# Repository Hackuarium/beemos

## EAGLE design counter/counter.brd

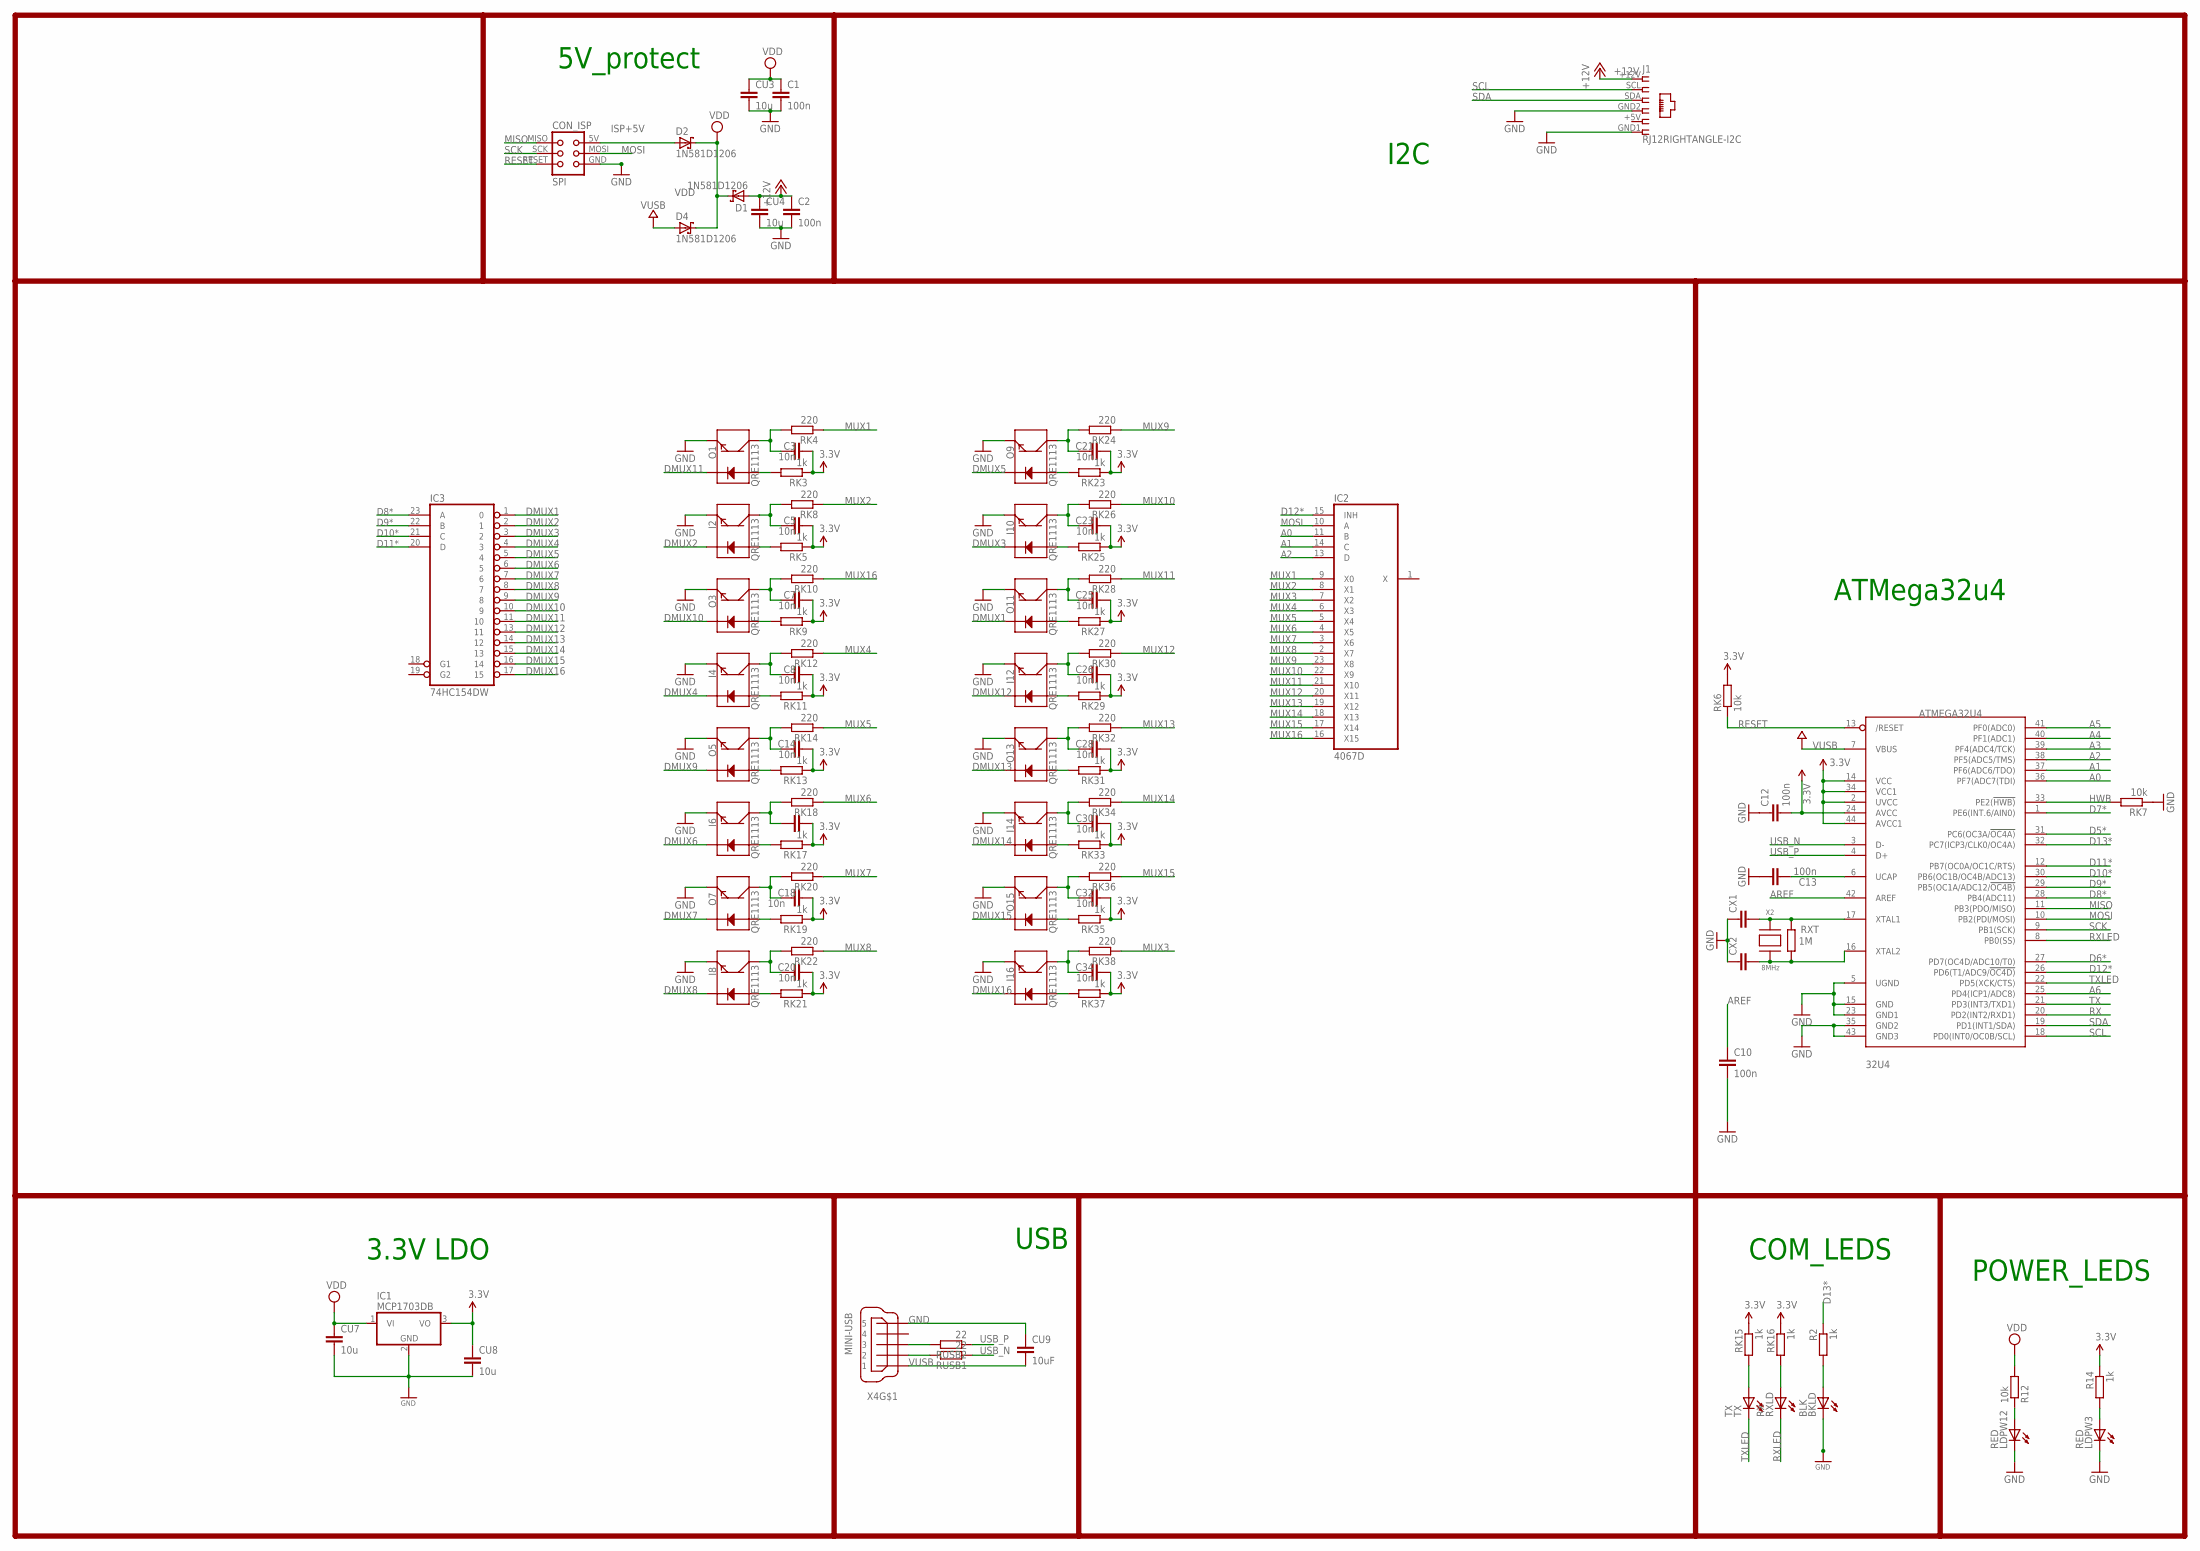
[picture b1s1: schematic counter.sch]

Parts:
32U4: ATMEGA32U4; TQFP44
BKLD: BLK; CHIP-LED0805
C1, C2, C10, C12, C13: 100n; C0805
C3, C5, C7, C8, C14, C15, C18, C20, C21, C23, C25, C26, C28, C30, C32, C34: 10n; C0805
CON_ISP: SPI; TC2030-MCP-NL
CU3, CU4, CU7, CU8: 10u; C0805
CU9: 10uF; C0805
CX1, CX2: 22pF; C0805
D1, D2, D4: 1N581D1206; LED-1206
I2, I4, I6, I8, I10, I12, I14, I16: QRE1113
IC1: MCP1703DB; SOT223
IC2: 4067D; SO24W
IC3: 74HC154DW; SO24W
J1: RJ12RIGHTANGLE-I2C; RJ12-RIGHTANGLE-I2C
LDPW3, LDPW12: RED; CHIP-LED0805
O1, O3, O5, O7, O9, O11, O13, O15: QRE1113
R2, R14: 1k; R0805
R12: 10k; R0805
RK3, RK5, RK9, RK11, RK13, RK17, RK19, RK21, RK23, RK25, RK27, RK29, RK31, RK33, RK35, RK37: 1k; M0805
RK4, RK8, RK10, RK12, RK14, RK18, RK20, RK22, RK24, RK26, RK28, RK30, RK32, RK34, RK36, RK38: 220; M0805
RK6, RK7: 10k; M0805
RK15, RK16: 1k; R0805
RUSB1, RUSB2: 22; M0805
RXLD: RX; CHIP-LED0805
RXT: 1M; R0805
TX: TX; CHIP-LED0805
X2: 8MHz; NX6035
X4: MINI-USB; 32005-201

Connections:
3.3V: 32U4.2 (UVCC), 32U4.14 (VCC), 32U4.24 (AVCC), 32U4.34 (VCC1), 32U4.44 (AVCC1), C3.2, C5.2, C7.2, C8.2, C12.2, C14.2, C15.2, C18.2, C20.2, C21.2, C23.2, C25.2, C26.2, C28.2, C30.2, C32.2, C34.2, CU8.1, IC1.3 (VO), R14.1, RK3.1, RK5.1, RK6.2, RK9.1, RK11.1, RK13.1, RK15.1, RK16.1, RK17.1, RK19.1, RK21.1, RK23.1, RK25.1, RK27.1, RK29.1, RK31.1, RK33.1, RK35.1, RK37.1
5: J1.+5V (5)
+12V: C2.1, CU4.1, D1.A, J1.+12V (1)
A0: 32U4.36 (PF7(ADC7(TDI)), IC2.11 (B)
A1: 32U4.37 (PF6(ADC6/TDO)), IC2.14 (C)
A2: 32U4.38 (PF5(ADC5/TMS)), IC2.13 (D)
A3: 32U4.39 (PF4(ADC4/TCK))
A4: 32U4.40 (PF1(ADC1))
A5: 32U4.41 (PF0(ADC0))
A6: 32U4.25 (PD4(ICP1/ADC8))
AREF: 32U4.42 (AREF), C10.1
D5*: 32U4.31 (PC6(OC3A/!OC4A))
D6*: 32U4.27 (PD7(OC4D/ADC10/T0))
D7*: 32U4.1 (PE6(INT.6/AIN0))
D8*: 32U4.28 (PB4(ADC11)), IC3.23 (A)
D9*: 32U4.29 (PB5(OC1A/ADC12/!OC4B)), IC3.22 (B)
D10*: 32U4.30 (PB6(OC1B/OC4B/ADC13)), IC3.21 (C)
D11*: 32U4.12 (PB7(OC0A/OC1C/RTS)), IC3.20 (D)
D12*: 32U4.26 (PD6(T1/ADC9/!OC4D)), IC2.15 (INH)
D13*: 32U4.32 (PC7(ICP3/CLK0/OC4A)), R2.1
DMUX1: IC3.1 (0), O11.2 (K)
DMUX2: I2.2 (K), IC3.2 (1)
DMUX3: I10.2 (K), IC3.3 (2)
DMUX4: I4.2 (K), IC3.4 (3)
DMUX5: IC3.5 (4), O9.2 (K)
DMUX6: I6.2 (K), IC3.6 (5)
DMUX7: IC3.7 (6), O7.2 (K)
DMUX8: I8.2 (K), IC3.8 (7)
DMUX9: IC3.9 (8), O5.2 (K)
DMUX10: IC3.10 (9), O3.2 (K)
DMUX11: IC3.11 (10), O1.2 (K)
DMUX12: I12.2 (K), IC3.13 (11)
DMUX13: IC3.14 (12), O13.2 (K)
DMUX14: I14.2 (K), IC3.15 (13)
DMUX15: IC3.16 (14), O15.2 (K)
DMUX16: I16.2 (K), IC3.17 (15)
GND: 32U4.5 (UGND), 32U4.15 (GND), 32U4.23 (GND1), 32U4.35 (GND2), 32U4.43 (GND3), BKLD.C, C1.2, C2.2, C10.2, C12.1, C13.1, CON_ISP.GND, CU3.2, CU4.2, CU7.2, CU8.2, CU9.1, CX1.1, CX2.1, I2.4 (E), I4.4 (E), I6.4 (E), I8.4 (E), I10.4 (E), I12.4 (E), I14.4 (E), I16.4 (E), IC1.2 (GND), IC3.12 (GND), J1.GND1 (6), J1.GND2 (4), LDPW3.C, LDPW12.C, O1.4 (E), O3.4 (E), O5.4 (E), O7.4 (E), O9.4 (E), O11.4 (E), O13.4 (E), O15.4 (E), RK7.1, X4.5
HWB: 32U4.33 (PE2(!HWB)), RK7.2
ISP+5V: CON_ISP.5V (VCC), D2.A
MISO: 32U4.11 (PB3(PDO/MISO)), CON_ISP.MISO
MOSI: 32U4.10 (PB2(PDI/MOSI)), CON_ISP.MOSI, IC2.10 (A)
MUX1: IC2.9 (X0), RK4.1
MUX2: IC2.8 (X1), RK8.1
MUX3: IC2.7 (X2), RK38.1
MUX4: IC2.6 (X3), RK12.1
MUX5: IC2.5 (X4), RK14.1
MUX6: IC2.4 (X5), RK18.1
MUX7: IC2.3 (X6), RK20.1
MUX8: IC2.2 (X7), RK22.1
MUX9: IC2.23 (X8), RK24.1
MUX10: IC2.22 (X9), RK26.1
MUX11: IC2.21 (X10), RK28.1
MUX12: IC2.20 (X11), RK30.1
MUX13: IC2.19 (X12), RK32.1
MUX14: IC2.18 (X13), RK34.1
MUX15: IC2.17 (X14), RK36.1
MUX16: IC2.16 (X15), RK10.1
unnamed: 32U4.6 (UCAP), C13.2
unnamed: O3.1 (A), RK9.2
unnamed: BKLD.A, R2.2
unnamed: O1.1 (A), RK3.2
unnamed: C3.1, O1.3 (C), RK4.2
unnamed: LDPW12.A, R12.1
unnamed: I2.1 (A), RK5.2
unnamed: C5.1, I2.3 (C), RK8.2
unnamed: C7.1, O3.3 (C), RK10.2
unnamed: I4.1 (A), RK11.2
unnamed: RK15.2, TX.A
unnamed: C8.1, I4.3 (C), RK12.2
unnamed: O9.1 (A), RK23.2
unnamed: O5.1 (A), RK13.2
unnamed: C14.1, O5.3 (C), RK14.2
unnamed: RK16.2, RXLD.A
unnamed: I6.1 (A), RK17.2
unnamed: C15.1, I6.3 (C), RK18.2
unnamed: C21.1, O9.3 (C), RK24.2
unnamed: O7.1 (A), RK19.2
unnamed: C18.1, O7.3 (C), RK20.2
unnamed: LDPW3.A, R14.2
unnamed: I10.1 (A), RK25.2
unnamed: C23.1, I10.3 (C), RK26.2
unnamed: I8.1 (A), RK21.2
unnamed: C20.1, I8.3 (C), RK22.2
unnamed: O11.1 (A), RK27.2
unnamed: C25.1, O11.3 (C), RK28.2
unnamed: 32U4.17 (XTAL1), CX1.2, RXT.2, X2.P$2
unnamed: I12.1 (A), RK29.2
unnamed: C26.1, I12.3 (C), RK30.2
unnamed: O13.1 (A), RK31.2
unnamed: C28.1, O13.3 (C), RK32.2
unnamed: I14.1 (A), RK33.2
unnamed: C30.1, I14.3 (C), RK34.2
unnamed: O15.1 (A), RK35.2
unnamed: C32.1, O15.3 (C), RK36.2
unnamed: I16.1 (A), RK37.2
unnamed: C34.1, I16.3 (C), RK38.2
RESET: 32U4.13 (/RESET), CON_ISP.RESET, RK6.1
RX: 32U4.20 (PD2(INT2/RXD1))
RXLED: 32U4.8 (PB0(SS)), RXLD.C
SCK: 32U4.9 (PB1(SCK)), CON_ISP.SCK
SCL: 32U4.18 (PD0(INT0/OC0B/SCL)), J1.SCL (2)
SDA: 32U4.19 (PD1(INT1/SDA)), J1.SDA (3)
TX: 32U4.21 (PD3(INT3/TXD1))
TXLED: 32U4.22 (PD5(XCK/CTS)), TX.C
USBC_N: RUSB1.2, X4.2
USBC_P: RUSB2.2, X4.3
USB_N: 32U4.3 (D-), RUSB1.1
USB_P: 32U4.4 (D+), RUSB2.1
VCC: IC3.24 (VCC)
VDD: C1.1, CU3.1, CU7.1, D1.C, D2.C, D4.C, IC1.1 (VI), IC2.24 (VDD), R12.2
VSS: IC2.12 (VSS)
VUSB: 32U4.7 (VBUS), CU9.2, D4.A, X4.1
XTAL1: 32U4.16 (XTAL2), CX2.2, RXT.1, X2.P$1

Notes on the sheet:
USB
I2C
5V_protect
POWER_LEDS
COM_LEDS
3.3V LDO
ATMega32u4

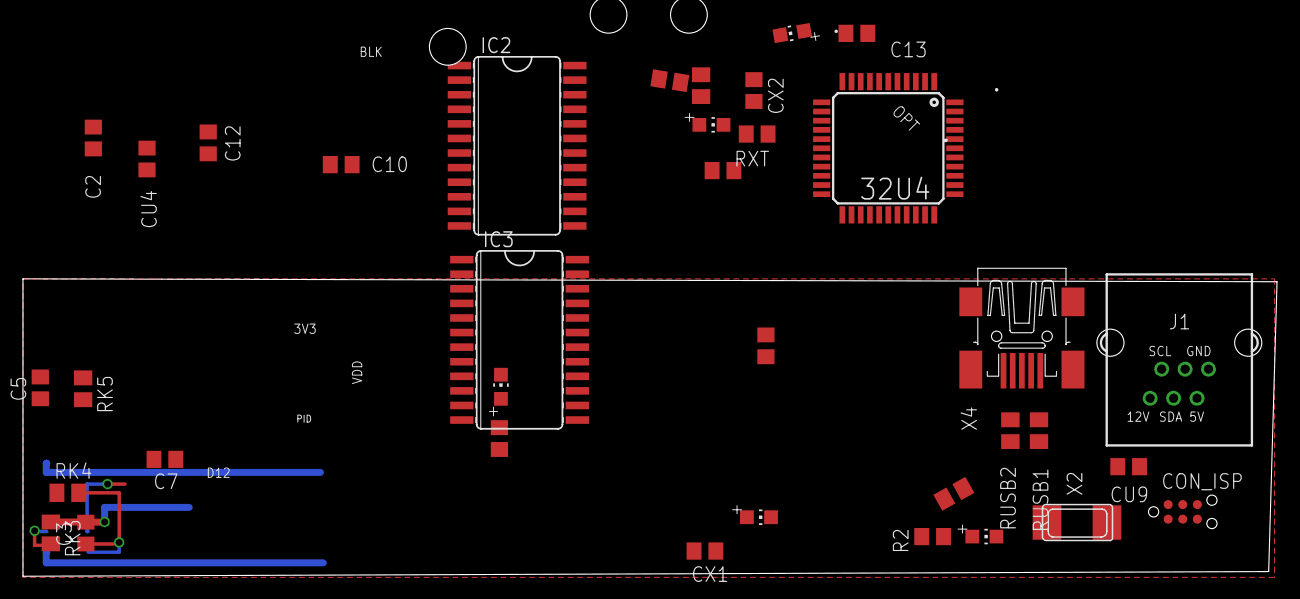
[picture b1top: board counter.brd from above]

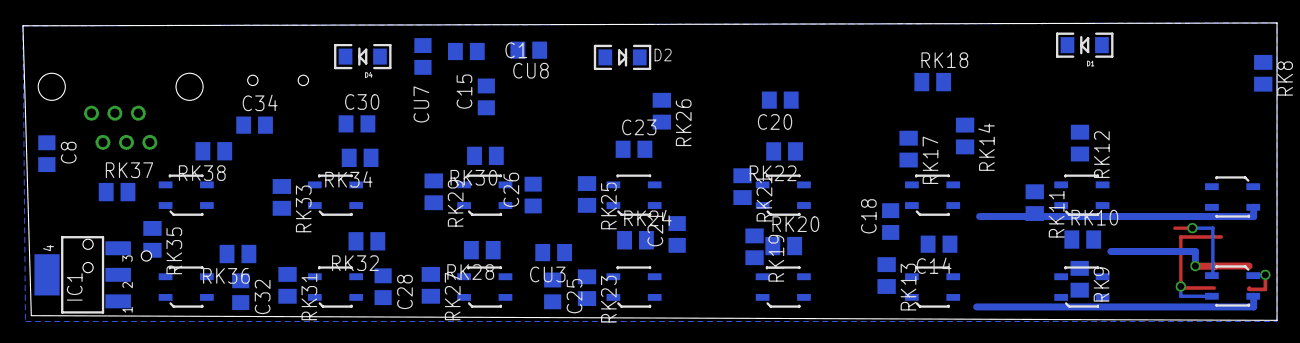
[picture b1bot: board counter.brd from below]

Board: 4 copper layers, 109.2 x 25.9 mm, 102 parts (66 on the bottom side), 101 nets.

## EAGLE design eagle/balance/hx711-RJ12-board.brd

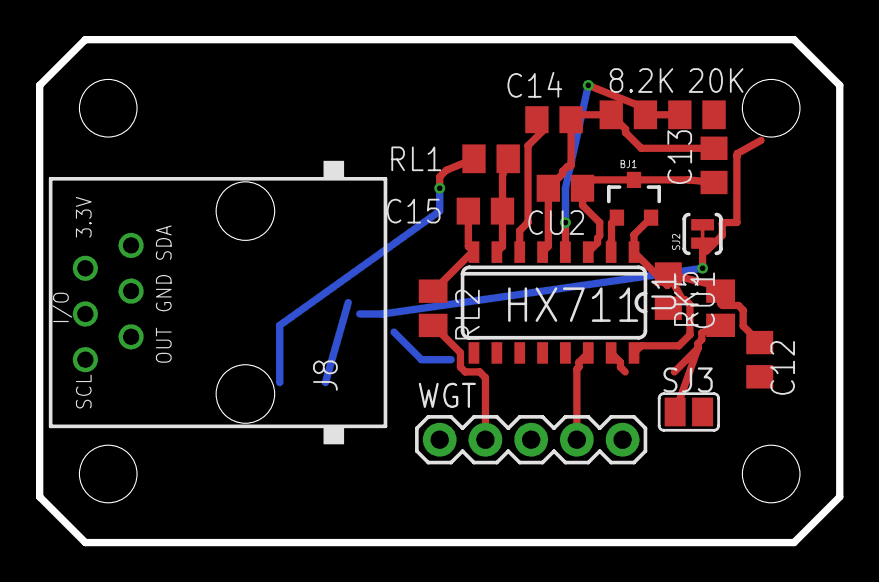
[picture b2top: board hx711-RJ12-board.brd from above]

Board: 2 copper layers, 44.5 x 27.9 mm, 17 parts (0 on the bottom side), 12 nets.

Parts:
8.2K: 8.2k; M0805
20K: 20k; M0805
BJ1: MMBT4403; SOT23-3
C12, C13, C14, C15: 100n; C0805
CU1, CU2: 10u; C0805
J8: RJ123.3; RJ12-STRAIGHT-3.3
RK5: 10k; M0805
RL1, RL2: 100; M0805
SJ2: PAD-JUMPER-2-NC_BY_TRACE_YES_SILK
SJ3: SJ
U1: HX711; SO16
WGT: 1X05

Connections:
3.3V: BJ1.2, C12.1, CU1.1, RK5.2, U1.1, U1.16
A+: RL2.2, WGT.2
A-: RL1.2, WGT.3
CN3: C14.2, U1.6
GND: C12.2, CU1.2, SJ2.1, SJ3.2, U1.14, WGT.1, WGT.4
LGND: 8.2K.1, C13.2, C14.1, CU2.2, SJ2.2, U1.5
unnamed: 20K.2, BJ1.3, C13.1, CU2.1, U1.3, WGT.5
unnamed: C15.2, RL1.1, U1.7
unnamed: BJ1.1, U1.2
unnamed: 8.2K.2, 20K.1, U1.4
unnamed: RK5.1, SJ3.1, U1.15
unnamed: C15.1, RL2.1, U1.8

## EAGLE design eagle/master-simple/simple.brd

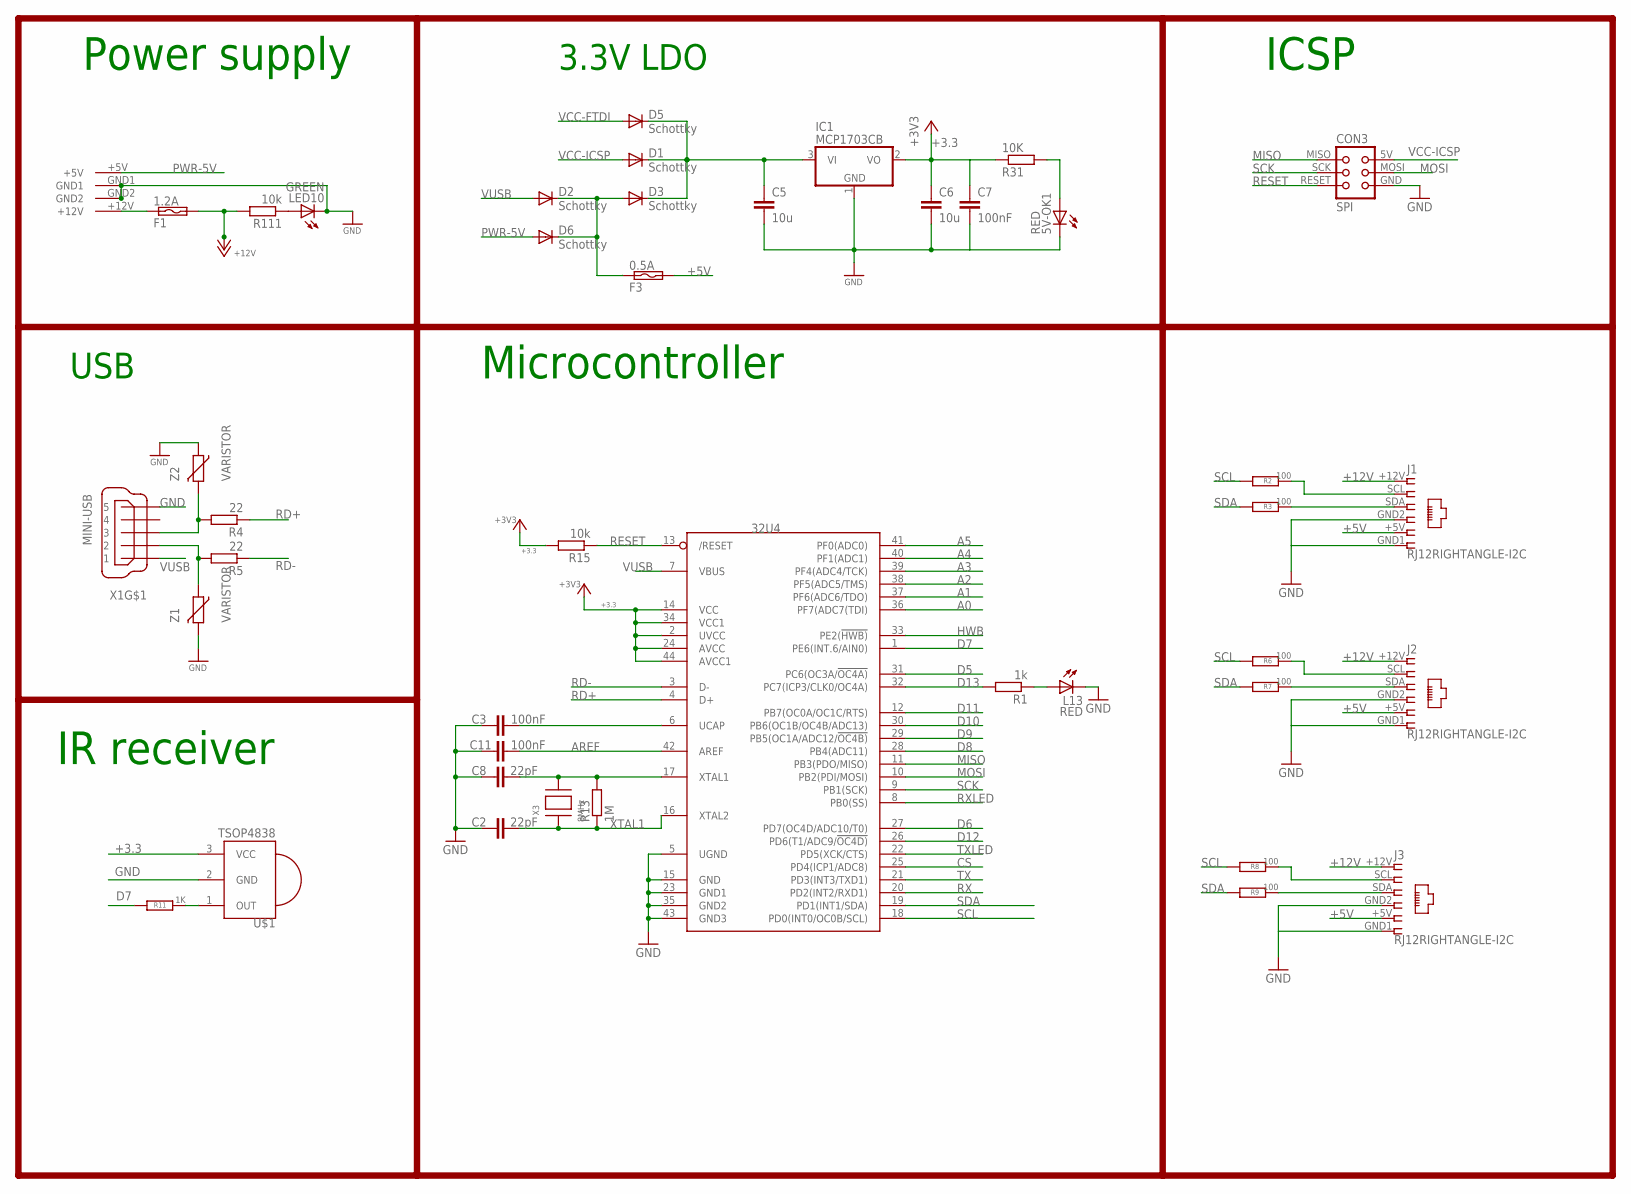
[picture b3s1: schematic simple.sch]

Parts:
5V-OK1: RED; CHIP-LED0805
C2, C8: 22pF; C0805K
C3, C11: 100nF; C0805K
C5, C6: 10u; C0805K; MPN 77-VJ1206V106ZXQTBC; LCSC C15850
C7: 100nF; C0805K; MPN 80-C1206C104K5R; LCSC C49678
CON3: SPI; TC2030-MCP-NL
D1, D2, D3, D5, D6: Schottky; SOD123; MPN 621-1N5819HW-F; LCSC C82544
F1: 1.2A; C1812
F3: 0.5A; C1812
IC1: MCP1703CB; SOT23; LCSC C53352
J1, J2, J3: RJ12RIGHTANGLE-I2C; RJ12-RIGHTANGLE-I2C
L13: RED; CHIP-LED0805
LED10: GREEN; CHIP-LED0805
R1: 1k; M0805
R2, R3, R6, R7, R8, R9: 100; R0805
R4, R5: 22; R0805; LCSC C17561
R11: 1K; R0805
R13: 1M; M0805
R15: 10k; M0805
R31: 10K; R0805
R111: 10k; R0805
U$1: TSOP4838; PNA460XM
U$4: 32U4; TQFP44
U$6: KPJX-4S-S
X1: MINI-USB; 32005-201; MPN 649-10033526-N3212LF; LCSC C46391
X3: 8MHz; NX6035
Z1, Z2: VARISTOR; CT/CN0603

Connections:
+3V3: C6.1, C7.1, IC1.2 (VO), R15.2, R31.1, U$1.3 (VCC), U$4.2 (UVCC), U$4.14 (VCC), U$4.24 (AVCC), U$4.34 (VCC1), U$4.44 (AVCC1); also elsewhere on the board
+5V: F3.2, J1.+5V (5), J2.+5V (5), J3.+5V (5); also elsewhere on the board
+12V: F1.2, J1.+12V (1), J2.+12V (1), J3.+12V (1), R111.2
+XV: C5.1, D1.C, D3.C, D5.C, IC1.3 (VI)
A0: U$4.36 (PF7(ADC7(TDI))
A1: U$4.37 (PF6(ADC6/TDO))
A2: U$4.38 (PF5(ADC5/TMS))
A3: U$4.39 (PF4(ADC4/TCK))
A4: U$4.40 (PF1(ADC1))
A5: U$4.41 (PF0(ADC0))
AREF: C11.1, U$4.42 (AREF)
CS: U$4.25 (PD4(ICP1/ADC8))
D5: U$4.31 (PC6(OC3A/!OC4A))
D6: U$4.27 (PD7(OC4D/ADC10/T0))
D7: R11.2, U$4.1 (PE6(INT.6/AIN0))
D8: U$4.28 (PB4(ADC11))
D9: U$4.29 (PB5(OC1A/ADC12/!OC4B))
D10: U$4.30 (PB6(OC1B/OC4B/ADC13))
D11: U$4.12 (PB7(OC0A/OC1C/RTS))
D12: U$4.26 (PD6(T1/ADC9/!OC4D))
D13: R1.2, U$4.32 (PC7(ICP3/CLK0/OC4A))
GND: 5V-OK1.C, C2.1, C3.1, C5.2, C6.2, C7.2, C8.1, C11.2, CON3.GND, IC1.1 (GND), J1.GND1 (6), J1.GND2 (4), J2.GND1 (6), J2.GND2 (4), J3.GND1 (6), J3.GND2 (4), L13.C, LED10.C, U$1.2 (GND), U$4.5 (UGND), U$4.15 (GND), U$4.23 (GND1), U$4.35 (GND2), U$4.43 (GND3), U$6.GND1, U$6.GND2, X1.5, Z1.2, Z2.1; also elsewhere on the board
HWB: U$4.33 (PE2(!HWB))
MISO: CON3.MISO, U$4.11 (PB3(PDO/MISO))
MOSI: CON3.MOSI, U$4.10 (PB2(PDI/MOSI))
unnamed: J2.SCL (2), R6.1
unnamed: J1.SCL (2), R2.1
unnamed: J1.SDA (3), R3.1
unnamed: L13.A, R1.1
unnamed: D2.C, D3.A, D6.C, F3.1
unnamed: J2.SDA (3), R7.1
unnamed: J3.SCL (2), R8.1
unnamed: J3.SDA (3), R9.1
unnamed: R11.1, U$1.1 (OUT)
unnamed: 5V-OK1.A, R31.2
unnamed: C3.2, U$4.6 (UCAP)
unnamed: F1.1, U$6.+12V
unnamed: C8.2, R13.2, U$4.17 (XTAL1), X3.P$2
unnamed: LED10.A, R111.1
PWR-5V: D6.A, U$6.+5V
RD+: R4.1, U$4.4 (D+)
RD-: R5.1, U$4.3 (D-)
RESET: CON3.RESET, R15.1, U$4.13 (/RESET)
RX: U$4.20 (PD2(INT2/RXD1)); also elsewhere on the board
RXLED: U$4.8 (PB0(SS))
SCK: CON3.SCK, U$4.9 (PB1(SCK))
SCL: R2.2, R6.2, R8.2, U$4.18 (PD0(INT0/OC0B/SCL))
SDA: R3.2, R7.2, R9.2, U$4.19 (PD1(INT1/SDA))
TX: U$4.21 (PD3(INT3/TXD1)); also elsewhere on the board
TXLED: U$4.22 (PD5(XCK/CTS))
USBC_N: R5.2, X1.2, Z1.1
USBC_P: R4.2, X1.3, Z2.2
VCC-ICSP: CON3.5V (VCC), D1.A
VUSB: D2.A, U$4.7 (VBUS), X1.1
XTAL1: C2.2, R13.1, U$4.16 (XTAL2), X3.P$1

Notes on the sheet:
IR receiver
ICSP
Microcontroller
USB
3.3V LDO
Power supply

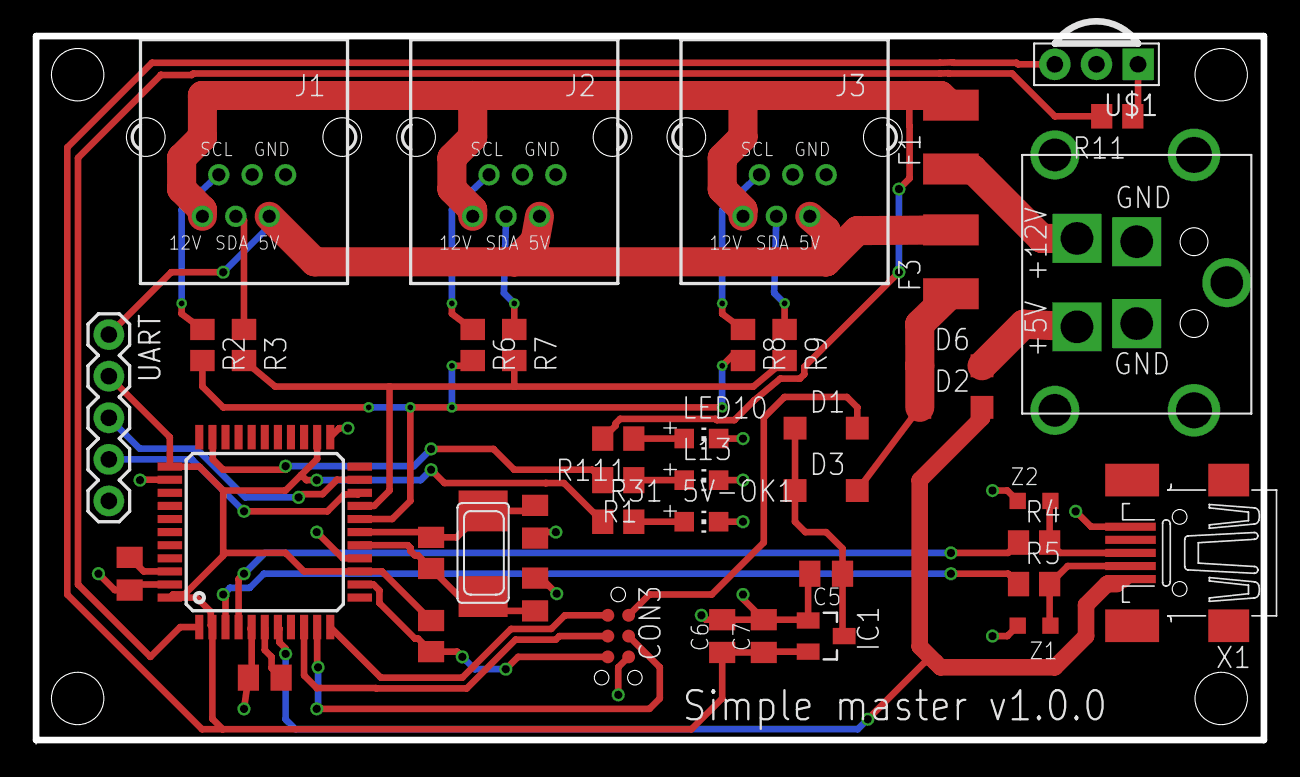
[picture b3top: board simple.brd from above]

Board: 2 copper layers, 75.0 x 43.0 mm, 43 parts (0 on the bottom side), 38 nets.

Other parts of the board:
UART: 1X05

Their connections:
+3V3: UART.2; also elsewhere on the board
+5V: UART.1; also elsewhere on the board
GND: UART.5; also elsewhere on the board
RX: UART.4; also elsewhere on the board
TX: UART.3; also elsewhere on the board

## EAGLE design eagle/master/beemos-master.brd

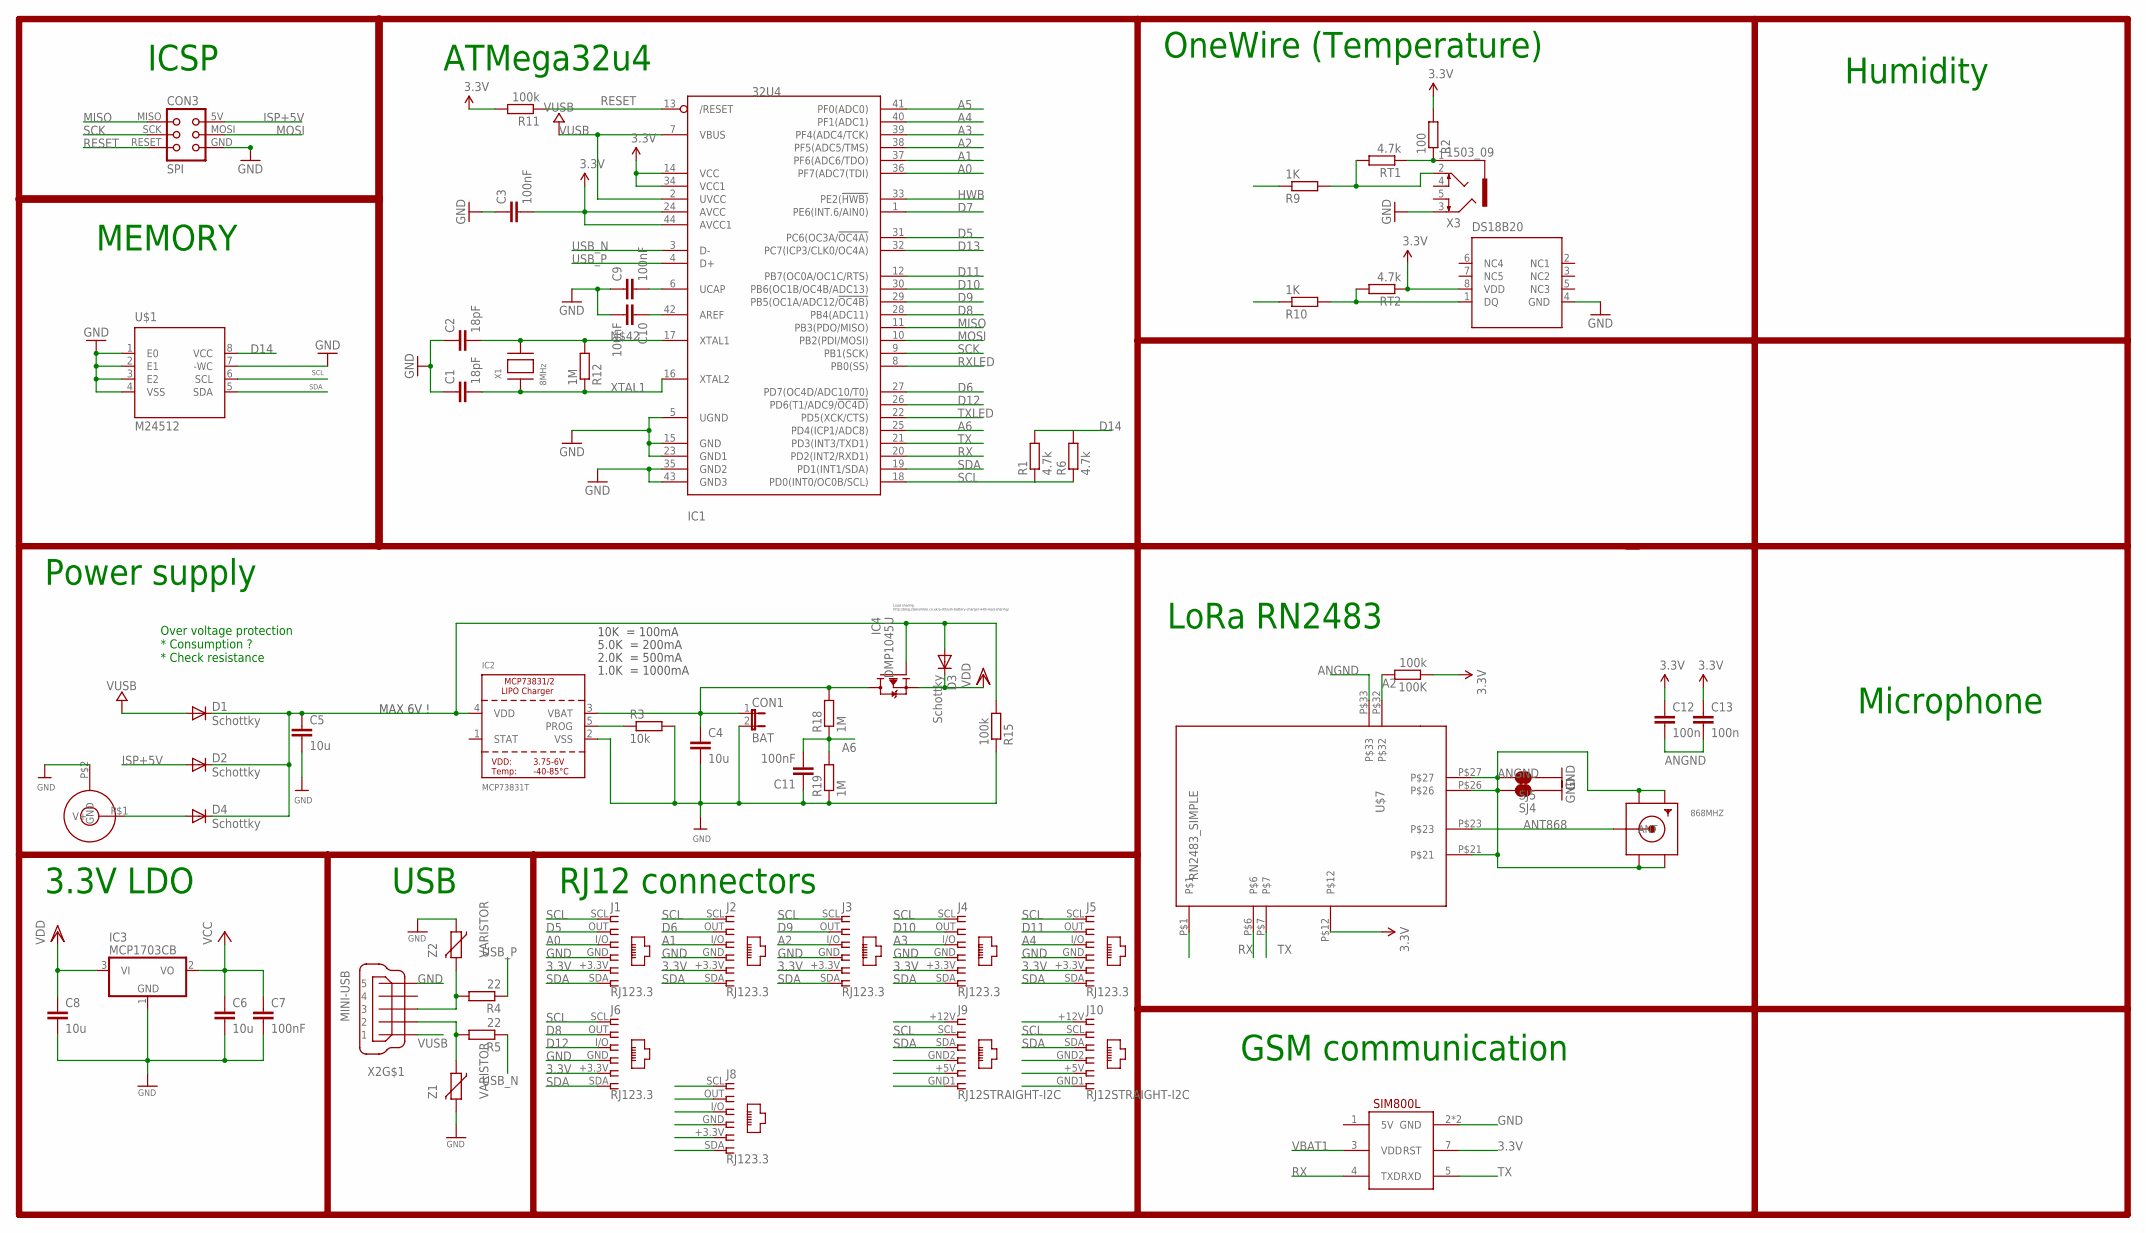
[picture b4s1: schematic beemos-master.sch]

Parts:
100K: 100k; R0805
868MHZ: SMACONNECTOR_EDGE_UFL; SMA_EDGELAUNCH_UFL
C1, C2: 18pF; C0805K; MPN 77-VJ1206A180JXXPBC; LCSC C1797
C3, C7, C9, C10, C11: 100nF; C0805K; MPN 80-C1206C104K5R; LCSC C49678
C4, C5, C6, C8: 10u; C0805K; MPN 77-VJ1206V106ZXQTBC; LCSC C15850
C12, C13: 100n; C0805
CON1: BAT; JP1
CON2: JACK_DC_BARREL; DC_BARREL
CON3: SPI; TC2030-MCP-NL
D1, D2, D3, D4: Schottky; SOD123; MPN 621-1N5819HW-F; LCSC C82544
IC1: 32U4; TQFP44; MPN 556-ATMEGA32U4RC-AU; LCSC C44854
IC2: MCP73831T; SOT23-5; MPN 579-MCP73831T-3ACIOT; LCSC C14879
IC3: MCP1703CB; SOT23; LCSC C53352
IC4: DMP1045U; SOT-23; MPN 621-DMP1045U-7; LCSC C96613
J1, J2, J3, J4, J5, J6, J8: RJ123.3; RJ12-STRAIGHT-3.3
J9, J10: RJ12STRAIGHT-I2C; RJ12-STRAIGHT-I2C
R1, R6: 4.7k; R0805
R2: 100; R0805
R3: 10k; R0805; LCSC C17414
R4, R5: 22; R0805; LCSC C17561
R9, R10: 1K; R0805
R11, R15: 100k; R0805; MPN RC1206FR-07100KL; LCSC C17407
R12, R18, R19: 1M; R0805; LCSC C17514
RT1, RT2: 4.7k; R0805
SJ4, SJ5: JUMPER-PAD-2-NC_BY_TRACE; PAD-JUMPER-2-NC_BY_TRACE_YES_SILK
U$1: M24512; SO8
U$6: SIM800L; SIP
U$7: RN2483_SIMPLE
U$8: DS18B20; MSOP8
X1: 8MHz; NX6035; MPN 729-F60800010; LCSC C122522
X2: MINI-USB; 32005-201; MPN 649-10033526-N3212LF; LCSC C46391
X3: 1503_09
Z1, Z2: VARISTOR; CT/CN0805; LCSC C79709

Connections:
3.3V: 100K.1, C3.2, C6.1, C7.1, C12.1, C13.1, IC1.14 (VCC), IC1.24 (AVCC), IC1.34 (VCC1), IC1.44 (AVCC1), IC3.2 (VO), J1.+3.3V (5), J2.+3.3V (5), J3.+3.3V (5), J4.+3.3V (5), J5.+3.3V (5), J6.+3.3V (5), R2.2, R11.2, RT2.1, U$6.7 (RST), U$7.P$12, U$8.8 (VDD)
A0: IC1.36 (PF7(ADC7(TDI)), J1.I/O (3)
A1: IC1.37 (PF6(ADC6/TDO)), J2.I/O (3)
A2: 100K.2, IC1.38 (PF5(ADC5/TMS)), J3.I/O (3), U$7.P$32
A3: IC1.39 (PF4(ADC4/TCK)), J4.I/O (3)
A4: IC1.40 (PF1(ADC1)), J5.I/O (3)
A5: IC1.41 (PF0(ADC0))
A6: C11.2, IC1.25 (PD4(ICP1/ADC8)), R18.1, R19.2
A7: R9.1
ANGND: 868MHZ.GND@1 (GND1), 868MHZ.GND@2 (GND2), 868MHZ.GND@3 (GND3), 868MHZ.GND@4 (GND4), C12.2, C13.2, SJ4.2, SJ5.2, U$7.P$1, U$7.P$21, U$7.P$26, U$7.P$27, U$7.P$33
ANT868: 868MHZ.P (ANT), U$7.P$23
AREF: C10.1, IC1.42 (AREF)
D5: IC1.31 (PC6(OC3A/!OC4A)), J1.OUT (2)
D6: IC1.27 (PD7(OC4D/ADC10/T0)), J2.OUT (2)
D7: IC1.1 (PE6(INT.6/AIN0))
D8: IC1.28 (PB4(ADC11)), J6.OUT (2)
D9: IC1.29 (PB5(OC1A/ADC12/!OC4B)), J3.OUT (2)
D10: IC1.30 (PB6(OC1B/OC4B/ADC13)), J4.OUT (2)
D11: IC1.12 (PB7(OC0A/OC1C/RTS)), J5.OUT (2)
D12: IC1.26 (PD6(T1/ADC9/!OC4D)), J6.I/O (3)
D12*: R10.1
D13: IC1.32 (PC7(ICP3/CLK0/OC4A))
D14: R1.2, R6.2, U$1.8 (VCC)
GND: C1.1, C2.1, C3.1, C4.2, C5.2, C6.2, C7.2, C8.2, C9.1, C10.2, C11.1, CON1.2, CON2.P$2 (GND), CON3.GND, IC1.5 (UGND), IC1.15 (GND), IC1.23 (GND1), IC1.35 (GND2), IC1.43 (GND3), IC2.2 (VSS), IC3.1 (GND), J1.GND (4), J2.GND (4), J3.GND (4), J4.GND (4), J5.GND (4), J6.GND (4), R3.2, R15.1, R19.1, SJ4.1, SJ5.1, U$1.1 (E0), U$1.2 (E1), U$1.3 (E2), U$1.4 (VSS), U$1.7 (-WC), U$6.2 (GND), U$6.6 (GND), U$8.4 (GND), X2.5, X3.3, Z1.2, Z2.1
HWB: IC1.33 (PE2(!HWB))
ISP+5V: CON3.5V (VCC), D2.A
MISO: CON3.MISO, IC1.11 (PB3(PDO/MISO))
MOSI: CON3.MOSI, IC1.10 (PB2(PDI/MOSI))
unnamed: C9.2, IC1.6 (UCAP)
unnamed: CON2.P$1 (V+), D4.A
unnamed: IC2.5 (PROG), R3.1
unnamed: R10.2, RT2.2, U$8.1 (DQ)
unnamed: R2.1, RT1.1, X3.1
unnamed: C5.1, D1.C, D2.C, D3.A, D4.C, IC2.4 (VDD), IC4.1 (G), R15.2
unnamed: R9.2, RT1.2, X3.2
unnamed: C2.2, IC1.17 (XTAL1), R12.2, X1.P$2
RESET: CON3.RESET, IC1.13 (/RESET), R11.1
RX: IC1.20 (PD2(INT2/RXD1)), U$6.4 (TXD), U$7.P$6
RXLED: IC1.8 (PB0(SS))
SCK: CON3.SCK, IC1.9 (PB1(SCK))
SCL: IC1.18 (PD0(INT0/OC0B/SCL)), J1.SCL (1), J2.SCL (1), J3.SCL (1), J4.SCL (1), J5.SCL (1), J6.SCL (1), J9.SCL (2), J10.SCL (2), R1.1, R6.1, U$1.6 (SCL)
SDA: IC1.19 (PD1(INT1/SDA)), J1.SDA (6), J2.SDA (6), J3.SDA (6), J4.SDA (6), J5.SDA (6), J6.SDA (6), J9.SDA (3), J10.SDA (3), U$1.5 (SDA)
TX: IC1.21 (PD3(INT3/TXD1)), U$6.5 (RXD), U$7.P$7
TXLED: IC1.22 (PD5(XCK/CTS))
USBC_N: R5.2, X2.2, Z1.1
USBC_P: R4.2, X2.3, Z2.2
USB_N: IC1.3 (D-), R5.1
USB_P: IC1.4 (D+), R4.1
VBAT1: C4.1, CON1.1, IC2.3 (VBAT), IC4.3 (D), R18.2, U$6.3 (VDD)
VDD: C8.1, D3.C, IC3.3 (VI), IC4.2 (S)
VUSB: D1.A, IC1.2 (UVCC), IC1.7 (VBUS), X2.1
XTAL1: C1.2, IC1.16 (XTAL2), R12.1, X1.P$1

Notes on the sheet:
USB
ICSP
ATMega32u4
3.3V LDO
10K = 100mA
5.0K = 200mA
2.0K = 500mA
1.0K = 1000mA
MAX 6V !
Load sharing: http://blog.zakkemble.co.uk/a-lithium-battery-charger-with-load-sharing/
RJ12 connectors
Over voltage protection * Consumption ? * Check resistance
Power supply
OneWire (Temperature)
Microphone
MEMORY
GSM communication
Humidity
LoRa RN2483

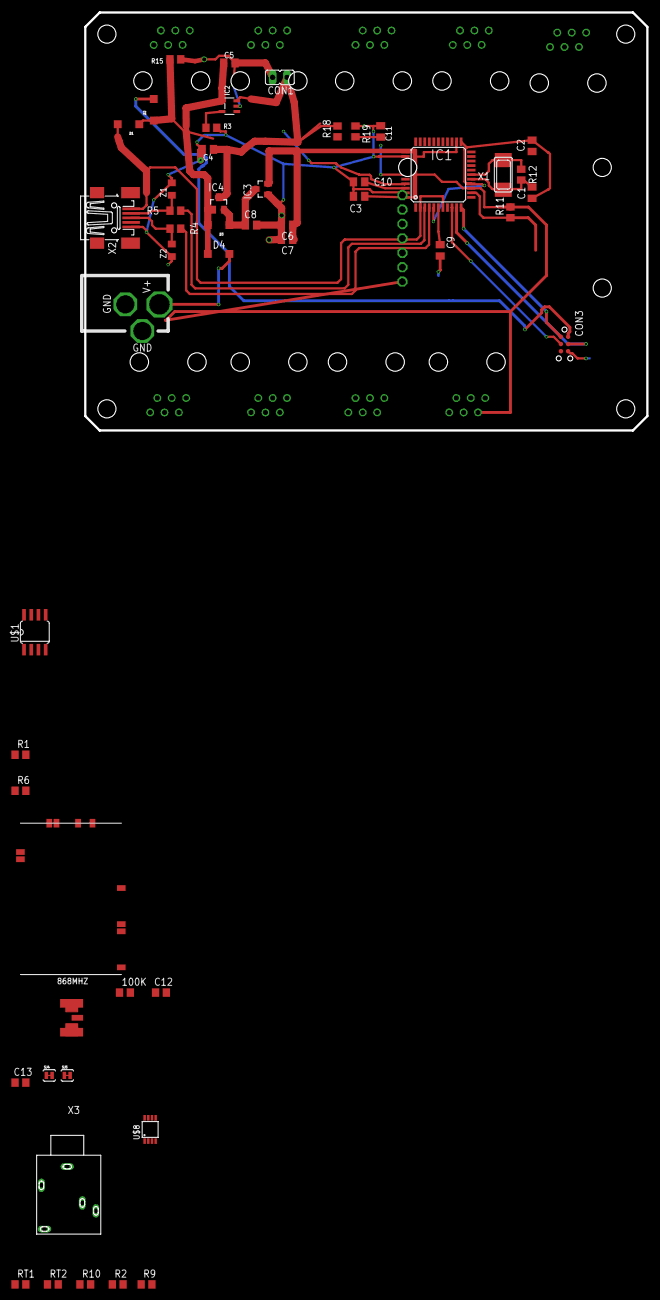
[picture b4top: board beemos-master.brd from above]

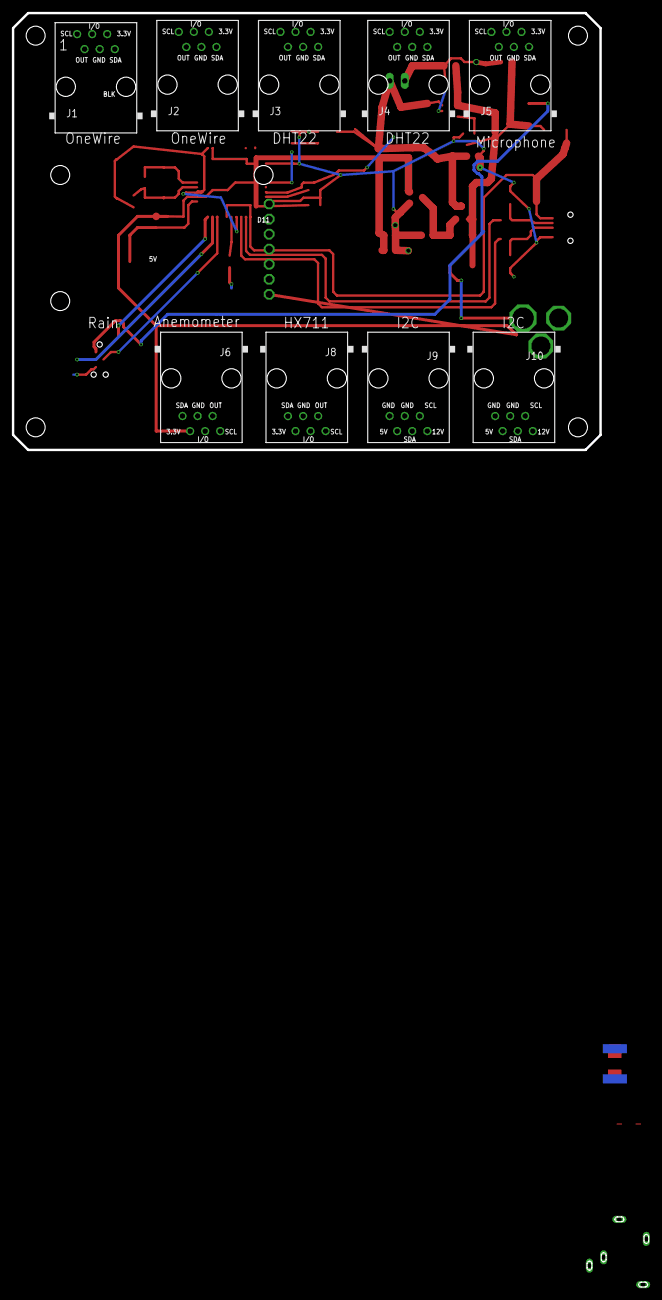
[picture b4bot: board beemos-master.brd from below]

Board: 2 copper layers, 107.2 x 214.8 mm, 61 parts (10 on the bottom side), 44 nets.

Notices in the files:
parts and their libraries:
lpatiny: ©2009 ROFA.cz - modified and updated by Robert Darlington ‹rdarlington@gmail.com›
SparkFun: Licensing: CC v3.0 Share-Alike You are welcome to use this library for commercial purposes.
